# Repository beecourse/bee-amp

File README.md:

bee-amp
=======

This [bee](https://github.com/beecourse) provides an operational **amp**lifier.
Depending on the populated parts, the module can serve as inverting or non-inverting amplifier or as an active rectifier.

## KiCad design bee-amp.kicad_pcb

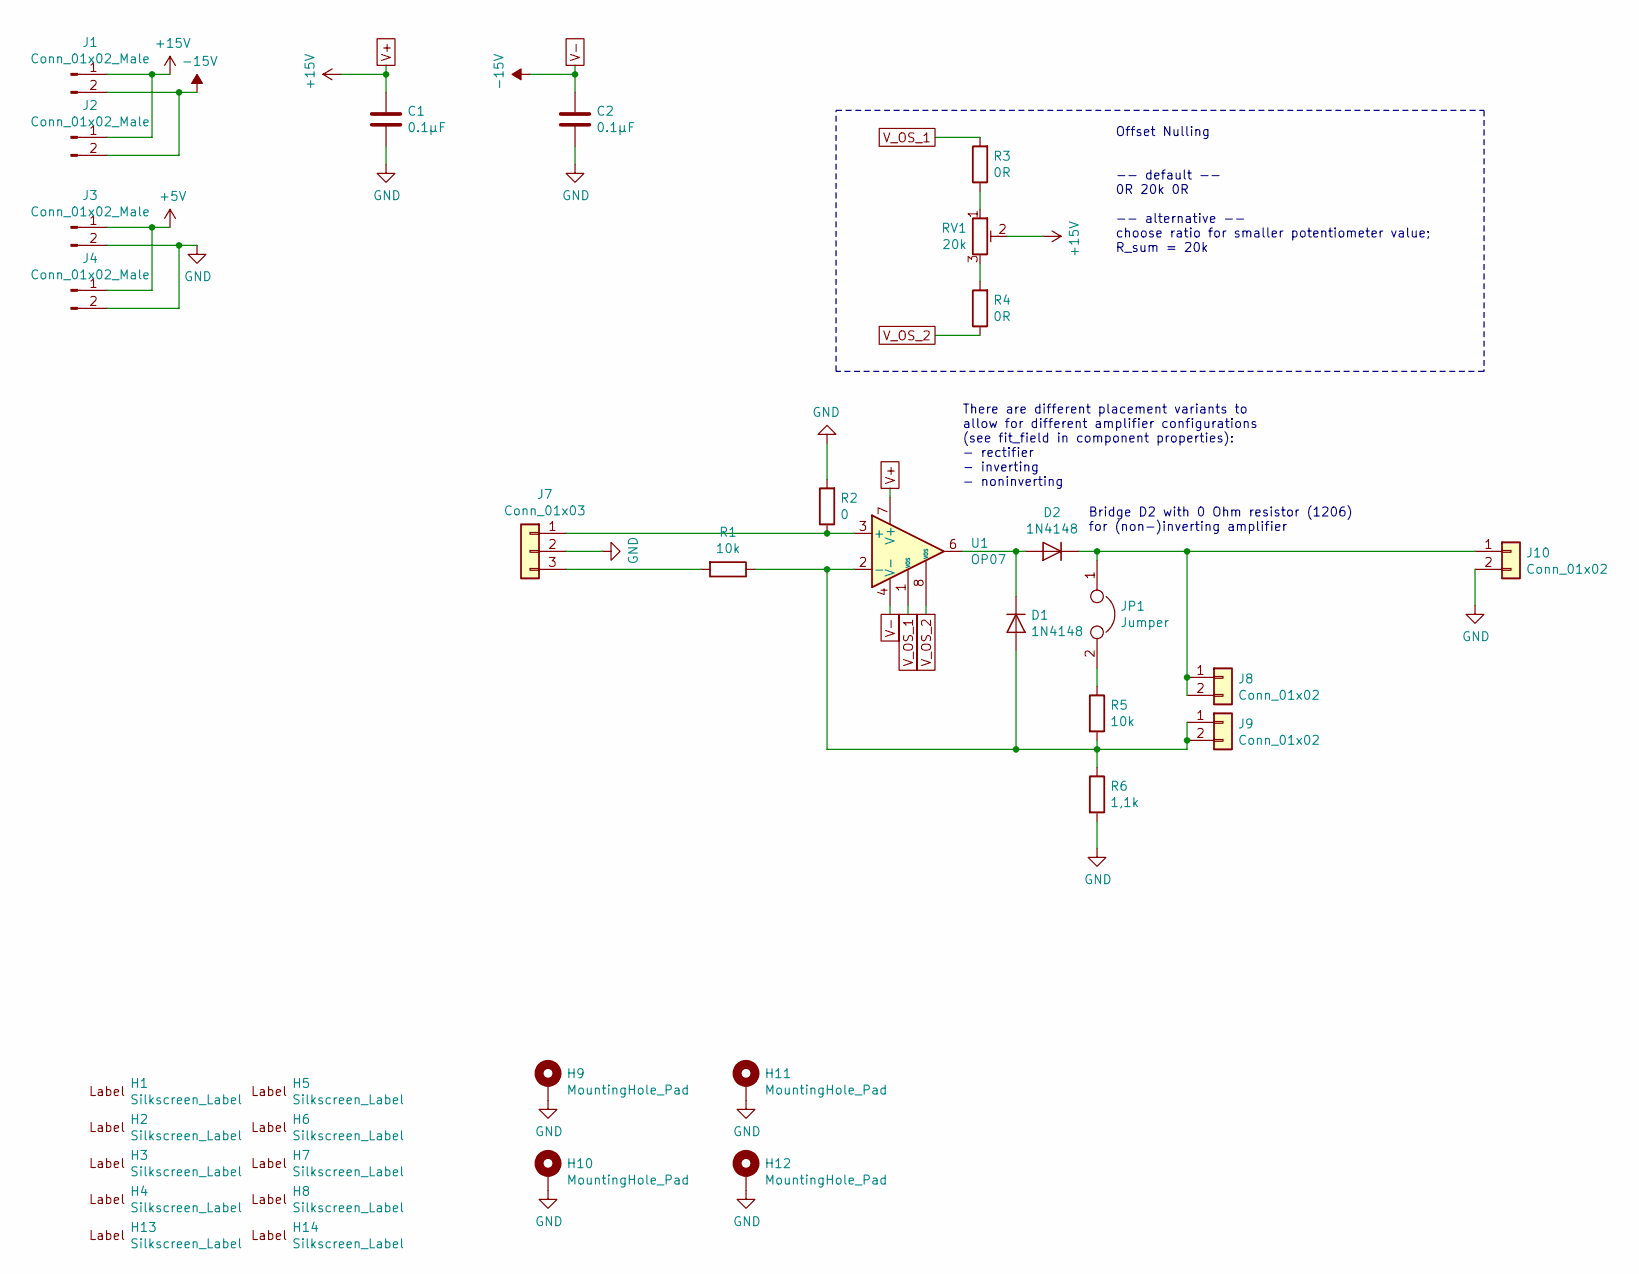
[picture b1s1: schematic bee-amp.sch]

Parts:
C1, C2: 0.1µF; C_0805_2012Metric_Pad1.15x1.40mm_HandSolder
D1, D2: 1N4148; D_MiniMELF
H1, H2: Silkscreen_Label; Text_U_B+_Silkscreen
H3, H4: Silkscreen_Label; Text_U_B-_Silkscreen
H5, H6: Silkscreen_Label; Text_U_B2_Silkscreen
H7, H8: Silkscreen_Label; Symbol_GND_Silkscreen
H9, H10, H11, H12: MountingHole_Pad; MountingHole_3.2mm_M3_ISO7380_Pad
H13: Silkscreen_Label; EMT-Logo_5.1x2.5mm_Silkscreen
H14: Silkscreen_Label; BEE-Logo_Silkscreen_small
J1, J2, J3, J4: Conn_01x02_Male; PinHeader_1x02_P2.54mm_Vertical
J7: Conn_01x03; PinHeader_1x03_P2.54mm_Vertical
J8, J9: Conn_01x02; PinSocket_1x02_P2.54mm_Vertical
J10: Conn_01x02; PinHeader_1x02_P2.54mm_Vertical
JP1: Jumper; PinHeader_1x02_P2.54mm_Vertical
R1, R5: 10k; R_0805_2012Metric_Pad1.15x1.40mm_HandSolder
R2: 0; R_0805_2012Metric_Pad1.15x1.40mm_HandSolder
R3, R4: 0R; R_0805_2012Metric_Pad1.15x1.40mm_HandSolder
R6: 1,1k; R_0805_2012Metric_Pad1.15x1.40mm_HandSolder
RV1: 20k; Potentiometer_Bourns_3314J_Vertical
U1: OP07; SOIC-8_3.9x4.9mm_P1.27mm

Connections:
+5V: J3.1, J4.1
GND: C1.2, C2.2, H9.1, H10.1, H11.1, H12.1, J3.2, J4.2, J7.2, J10.2, R2.2, R6.2
unnamed: D1.1 (K), D2.2 (A), U1.6
unnamed: D1.2 (A), J9.1, J9.2, R1.1, R5.2, R6.1, U1.2 (-)
unnamed: D2.1 (K), J8.1, J8.2, J10.1, JP1.1
unnamed: J7.1, R2.1, U1.3 (+)
unnamed: J7.3, R1.2
unnamed: JP1.2, R5.1
unnamed: R3.1, RV1.1
unnamed: R4.2, RV1.3
V+: C1.1, J1.1, J2.1, RV1.2, U1.7 (V+)
V-: C2.1, J1.2, J2.2, U1.4 (V-)
V_OS_1: R3.2, U1.1 (VOS)
V_OS_2: R4.1, U1.8 (VOS)

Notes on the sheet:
Offset Nulling -- default -- 0R 20k 0R -- alternative -- choose ratio for smaller potentiometer value; R_sum = 20k
There are different placement variants to allow for different amplifier configurations (see fit_field in component properties): - rectifier - inverting - noninverting
Bridge D2 with 0 Ohm resistor (1206) for (non-)inverting amplifier

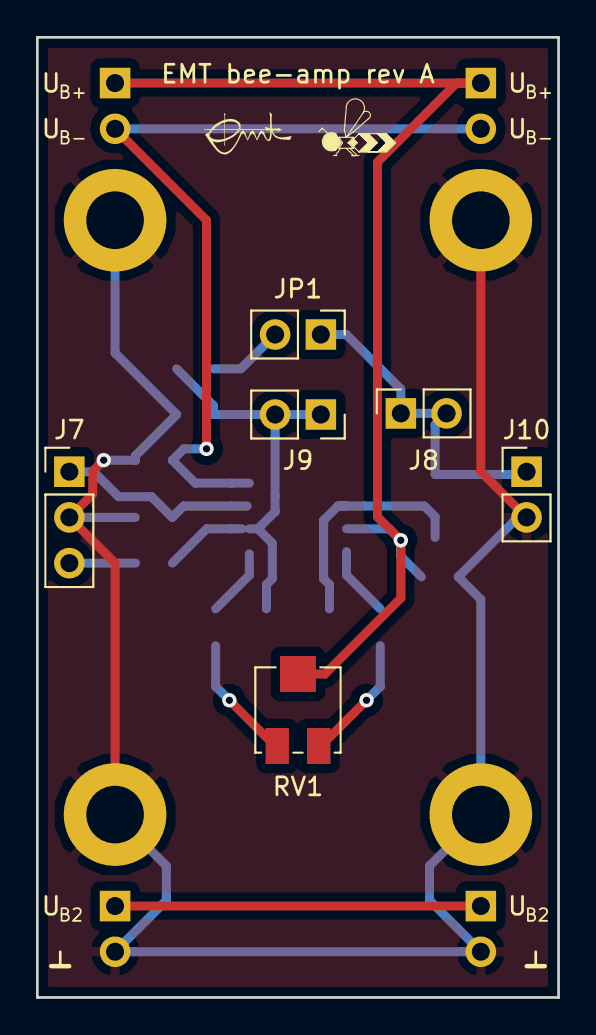
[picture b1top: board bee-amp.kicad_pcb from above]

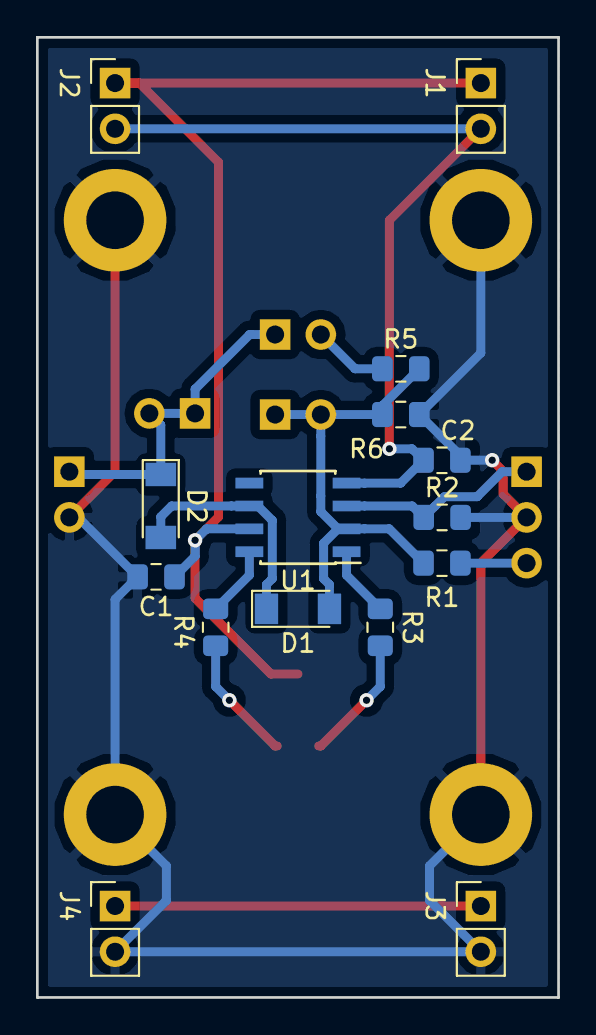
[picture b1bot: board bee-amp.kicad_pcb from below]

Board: 2 copper layers, 29.0 x 53.3 mm, 35 parts (15 on the bottom side), 14 nets.

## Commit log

2019-04-26 First commit - empty project.
2019-04-26 Add gitignore.
2019-04-26 schematic and basic layout
2019-04-30 Update lables and mounting holes.
2019-04-30 Update gitignore.
2019-05-02 Layout traces.
2019-05-02 Place refs on silkscreen.
2019-05-03 Add ground planes.
2019-05-03 Add text and logos.
2019-05-08 Add part values, numbers and placement variants.
2019-05-08 Unify part numbers.
2019-05-24 Update info on placement variants.
2019-07-16 Replace SO package by SOIC. Fixes #1.
2020-07-01 Relabel as bee specific.
2020-07-15 Add license.
2020-07-15 Add readme.
2023-03-17 Add figure showing top view of PCB
